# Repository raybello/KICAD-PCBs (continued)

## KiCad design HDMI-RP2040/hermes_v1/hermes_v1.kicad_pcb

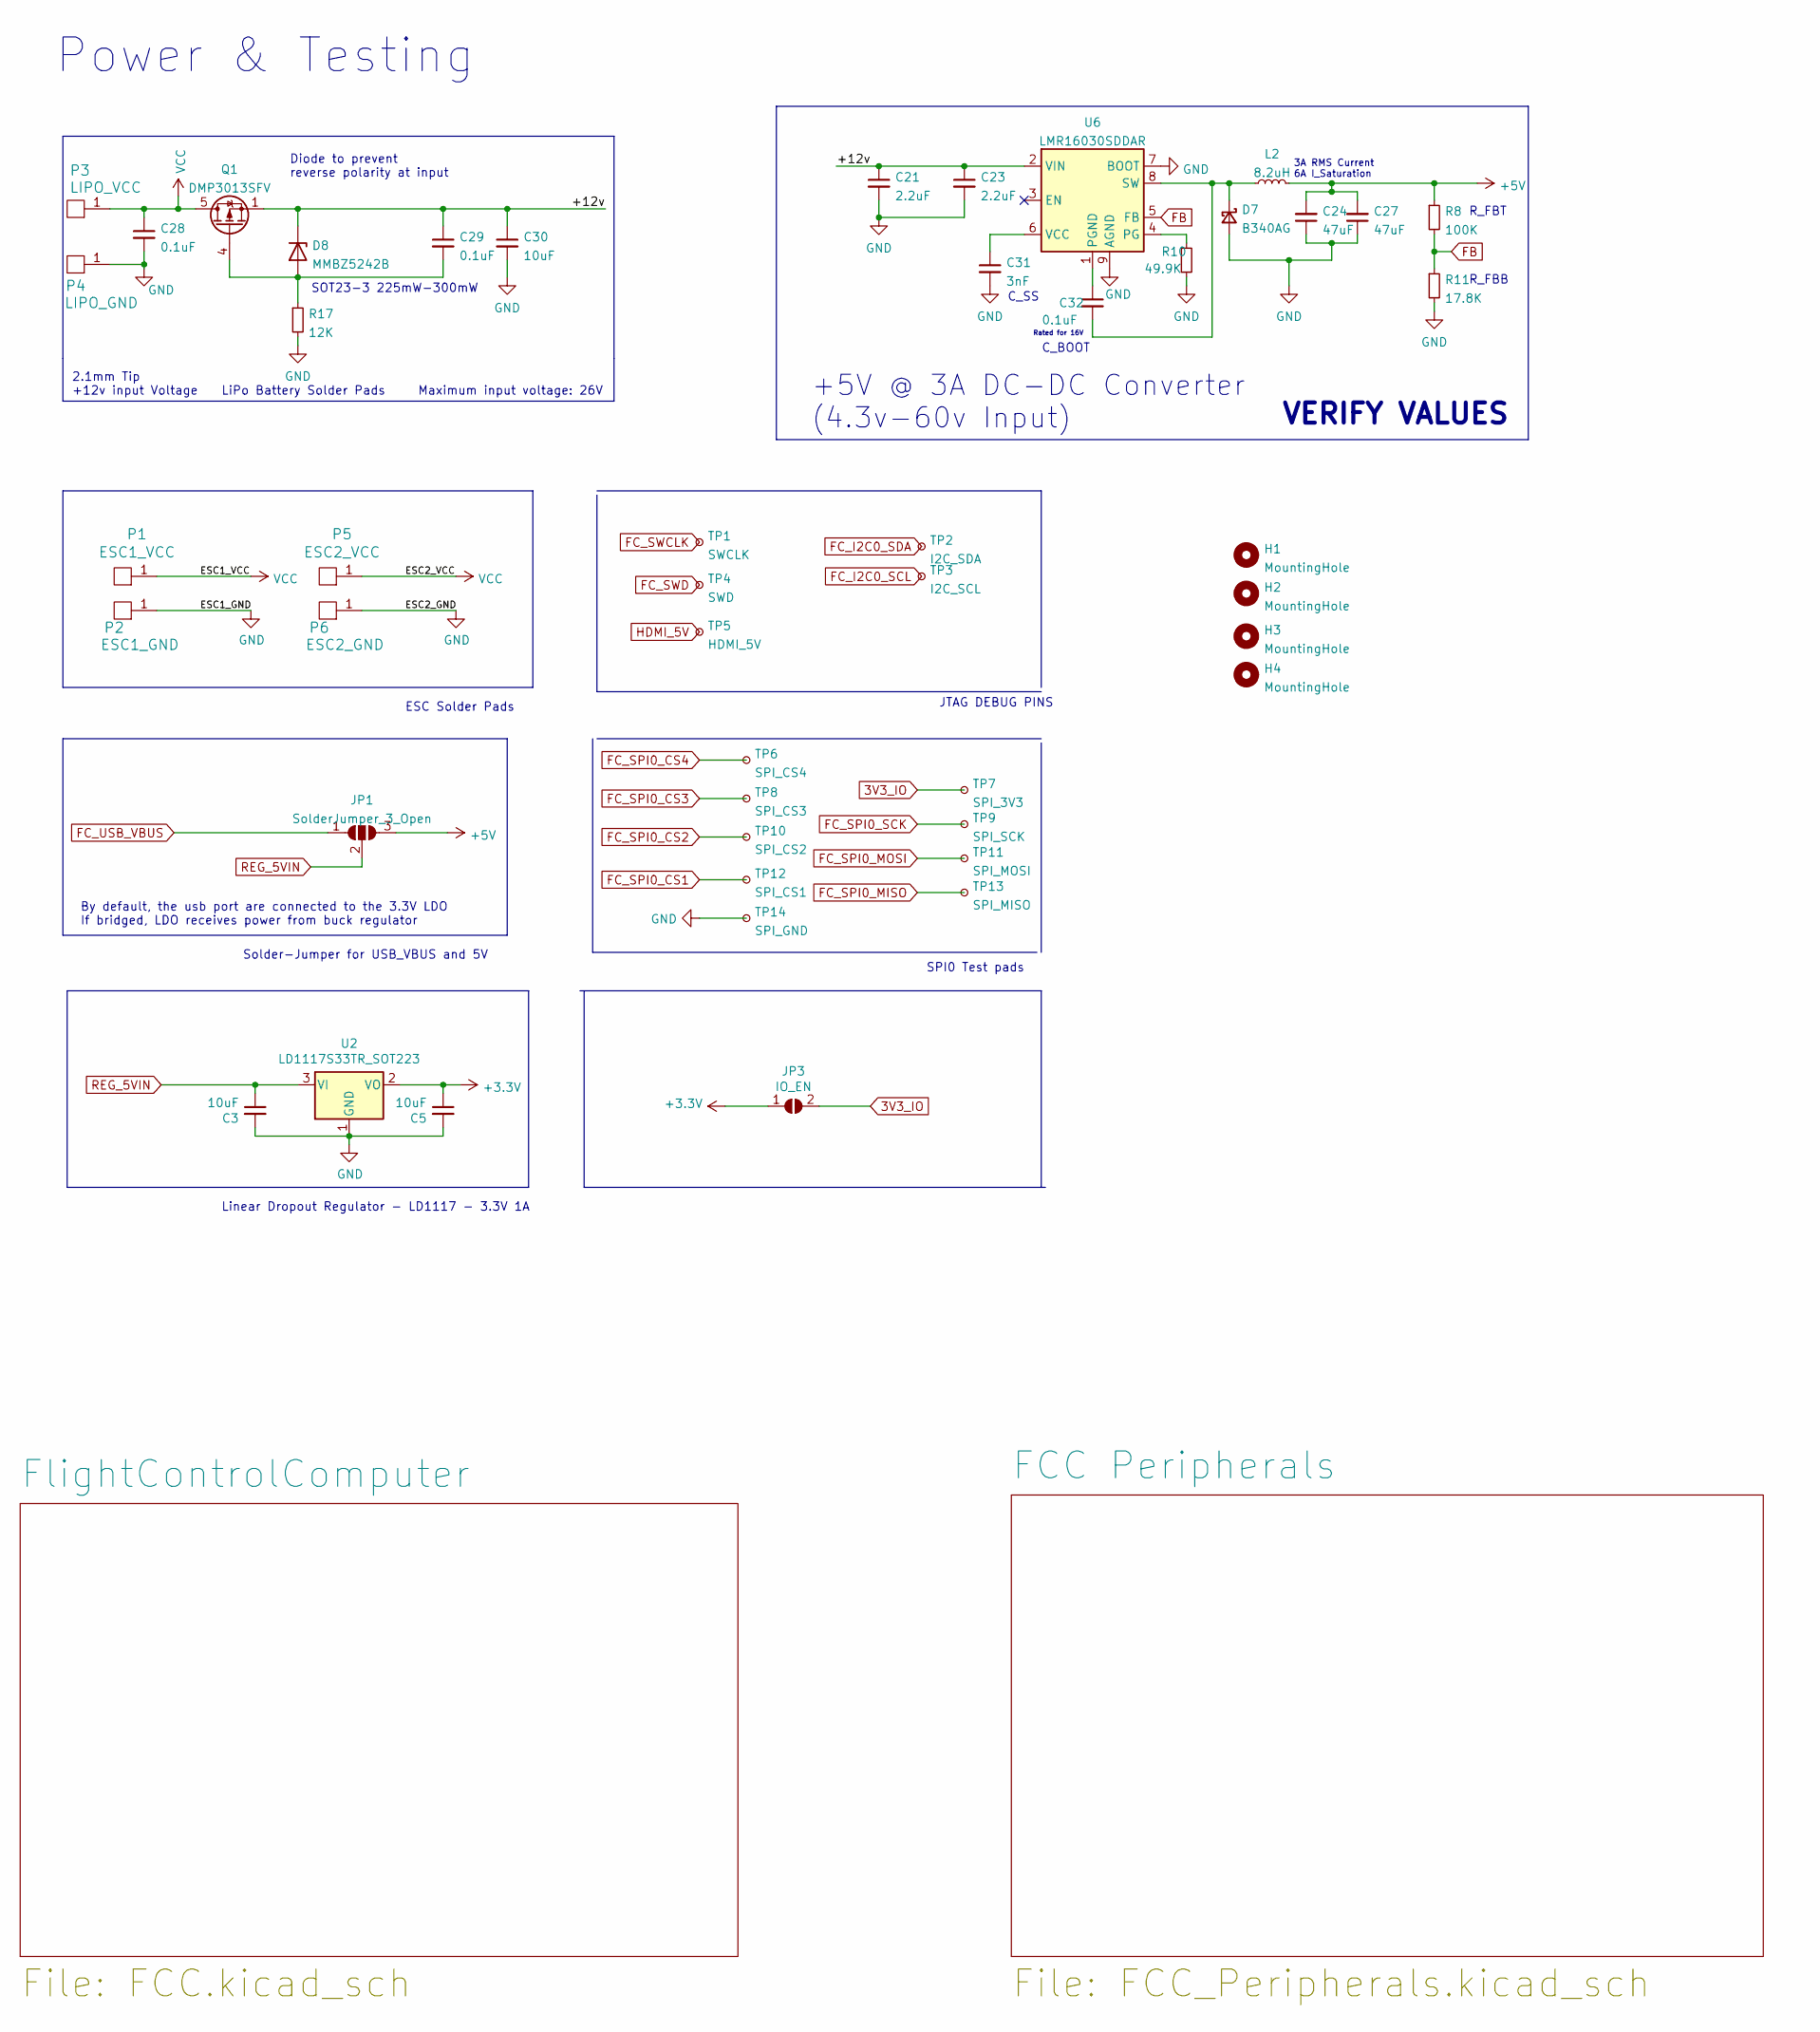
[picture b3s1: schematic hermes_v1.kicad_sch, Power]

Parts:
C3, C5: 10uF; C_0402_1005Metric_Pad0.74x0.62mm_HandSolder; LCSC C315248
C21, C23: 2.2uF; C_0402_1005Metric; LCSC C385887
C24, C27: 47uF; C_0402_1005Metric; LCSC C16780
C28, C29, C32: 0.1uF; C_0402_1005Metric; LCSC C129131
C30: 10uF; C_0402_1005Metric; LCSC C315248
C31: 3nF; C_0402_1005Metric; LCSC C2857967
D7: B340AG; D_SMB; LCSC C433997
D8: MMBZ5242B; D_SOT-23_ANK; LCSC C193729
H1, H2, H3, H4: MountingHole; MountingHole_3mm_Pad
JP1: SolderJumper_3_Open; SolderJumper-3_P1.3mm_Open_RoundedPad1.0x1.5mm_NumberLabels
JP3: IO_EN; SolderJumper-2_P1.3mm_Open_RoundedPad1.0x1.5mm
L2: 8.2uH; L_Bourns_SRP7028A_7.3x6.6mm; LCSC Mouser 652-SRP7028AA-8R2M
P1: ESC1_VCC; TestPoint_Pad_2.0x2.0mm
P2: ESC1_GND; TestPoint_Pad_D2.0mm
P3: LIPO_VCC; TestPoint_Pad_2.0x2.0mm
P4: LIPO_GND; TestPoint_Pad_D2.0mm
P5: ESC2_VCC; TestPoint_Pad_2.0x2.0mm
P6: ESC2_GND; TestPoint_Pad_D2.0mm
Q1: DMP3013SFV; Diodes_PowerDI3333-8; LCSC C461072
R8: 100K; R_0402_1005Metric; LCSC C144809
R10: 49.9K; R_0402_1005Metric; LCSC C2906873
R11: 17.8K; R_0402_1005Metric; LCSC C77605
R17: 12K; R_0402_1005Metric; LCSC C2909316
TP1: SWCLK; TestPoint_Pad_D1.0mm
TP2: I2C_SDA; TestPoint_Pad_D1.0mm
TP3: I2C_SCL; TestPoint_Pad_D1.0mm
TP4: SWD; TestPoint_Pad_D1.0mm
TP5: HDMI_5V; TestPoint_Pad_D1.0mm
TP6: SPI_CS4; TestPoint_Pad_D1.0mm
TP7: SPI_3V3; TestPoint_Pad_D1.0mm
TP8: SPI_CS3; TestPoint_Pad_D1.0mm
TP9: SPI_SCK; TestPoint_Pad_D1.0mm
TP10: SPI_CS2; TestPoint_Pad_D1.0mm
TP11: SPI_MOSI; TestPoint_Pad_D1.0mm
TP12: SPI_CS1; TestPoint_Pad_D1.0mm
TP13: SPI_MISO; TestPoint_Pad_D1.0mm
TP14: SPI_GND; TestPoint_Pad_D1.0mm
U2: LD1117S33TR_SOT223; SOT-223-3_TabPin2; LCSC C347229
U6: LMR16030SDDAR; Texas_HSOP-8-1EP_3.9x4.9mm_P1.27mm_ThermalVias; LCSC C136648

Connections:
3V3_IO: JP3.2 (B), TP7.1; also elsewhere on the board
+3V3: C5.1, JP3.1 (A), U2.2 (VO); also elsewhere on the board
+5V: C24.2, C27.2, JP1.3 (B), L2.2, R8.1; also elsewhere on the board
/+12v: C21.1, C23.1, C29.1, C30.1, D8.1 (K), Q1.1 (S), Q1.2 (S), Q1.3 (S), U6.2 (VIN)
FB: R8.2, R11.1, U6.5 (FB)
FC_I2C0_SCL: TP3.1; also elsewhere on the board
FC_I2C0_SDA: TP2.1; also elsewhere on the board
FC_SPI0_CS1: TP12.1; also elsewhere on the board
FC_SPI0_CS2: TP10.1; also elsewhere on the board
FC_SPI0_CS3: TP8.1; also elsewhere on the board
FC_SPI0_CS4: TP6.1; also elsewhere on the board
FC_SPI0_MISO: TP13.1; also elsewhere on the board
FC_SPI0_MOSI: TP11.1; also elsewhere on the board
FC_SPI0_SCK: TP9.1; also elsewhere on the board
FC_SWCLK: TP1.1; also elsewhere on the board
FC_SWD: TP4.1; also elsewhere on the board
FC_USB_VBUS: JP1.1 (A); also elsewhere on the board
GND: C3.2, C5.2, C21.2, C23.2, C24.1, C27.1, C28.2, C30.2, C31.2, D7.2 (A), P2.1 (PAD), P4.1 (PAD), P6.1 (PAD), R10.2, R11.2, R17.2, TP14.1, U2.1 (GND), U6.7 (BOOT), U6.9 (AGND); also elsewhere on the board
HDMI_5V: TP5.1; also elsewhere on the board
unnamed: C29.2, D8.2 (A), Q1.4 (G), R17.1
unnamed: C31.1, U6.6 (VCC)
unnamed: C32.1, U6.1 (PGND)
unnamed: C32.2, D7.1 (K), L2.1, U6.8 (SW)
unnamed: R10.1, U6.4 (PG)
REG_5VIN: C3.1, JP1.2 (C), U2.3 (VI)
VCC: C28.1, P1.1 (PAD), P3.1 (PAD), P5.1 (PAD), Q1.5 (D)

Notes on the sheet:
SOT23-3 225mW-300mW
R_FBB
2.1mm Tip +12v input Voltage
Maximum input voltage: 26V
SPI0 Test pads
R_FBT
Power & Testing
Rated for 16V
C_SS
+5V @ 3A DC-DC Converter (4.3v-60v Input)
C_BOOT
3A RMS Current 6A I_Saturation
LiPo Battery Solder Pads
VERIFY VALUES
Diode to prevent reverse polarity at input
Solder-Jumper for USB_VBUS and 5V
By default, the usb port are connected to the 3.3V LDO If bridged, LDO receives power from buck regulator
JTAG DEBUG PINS
ESC Solder Pads
Linear Dropout Regulator - LD1117 - 3.3V 1A

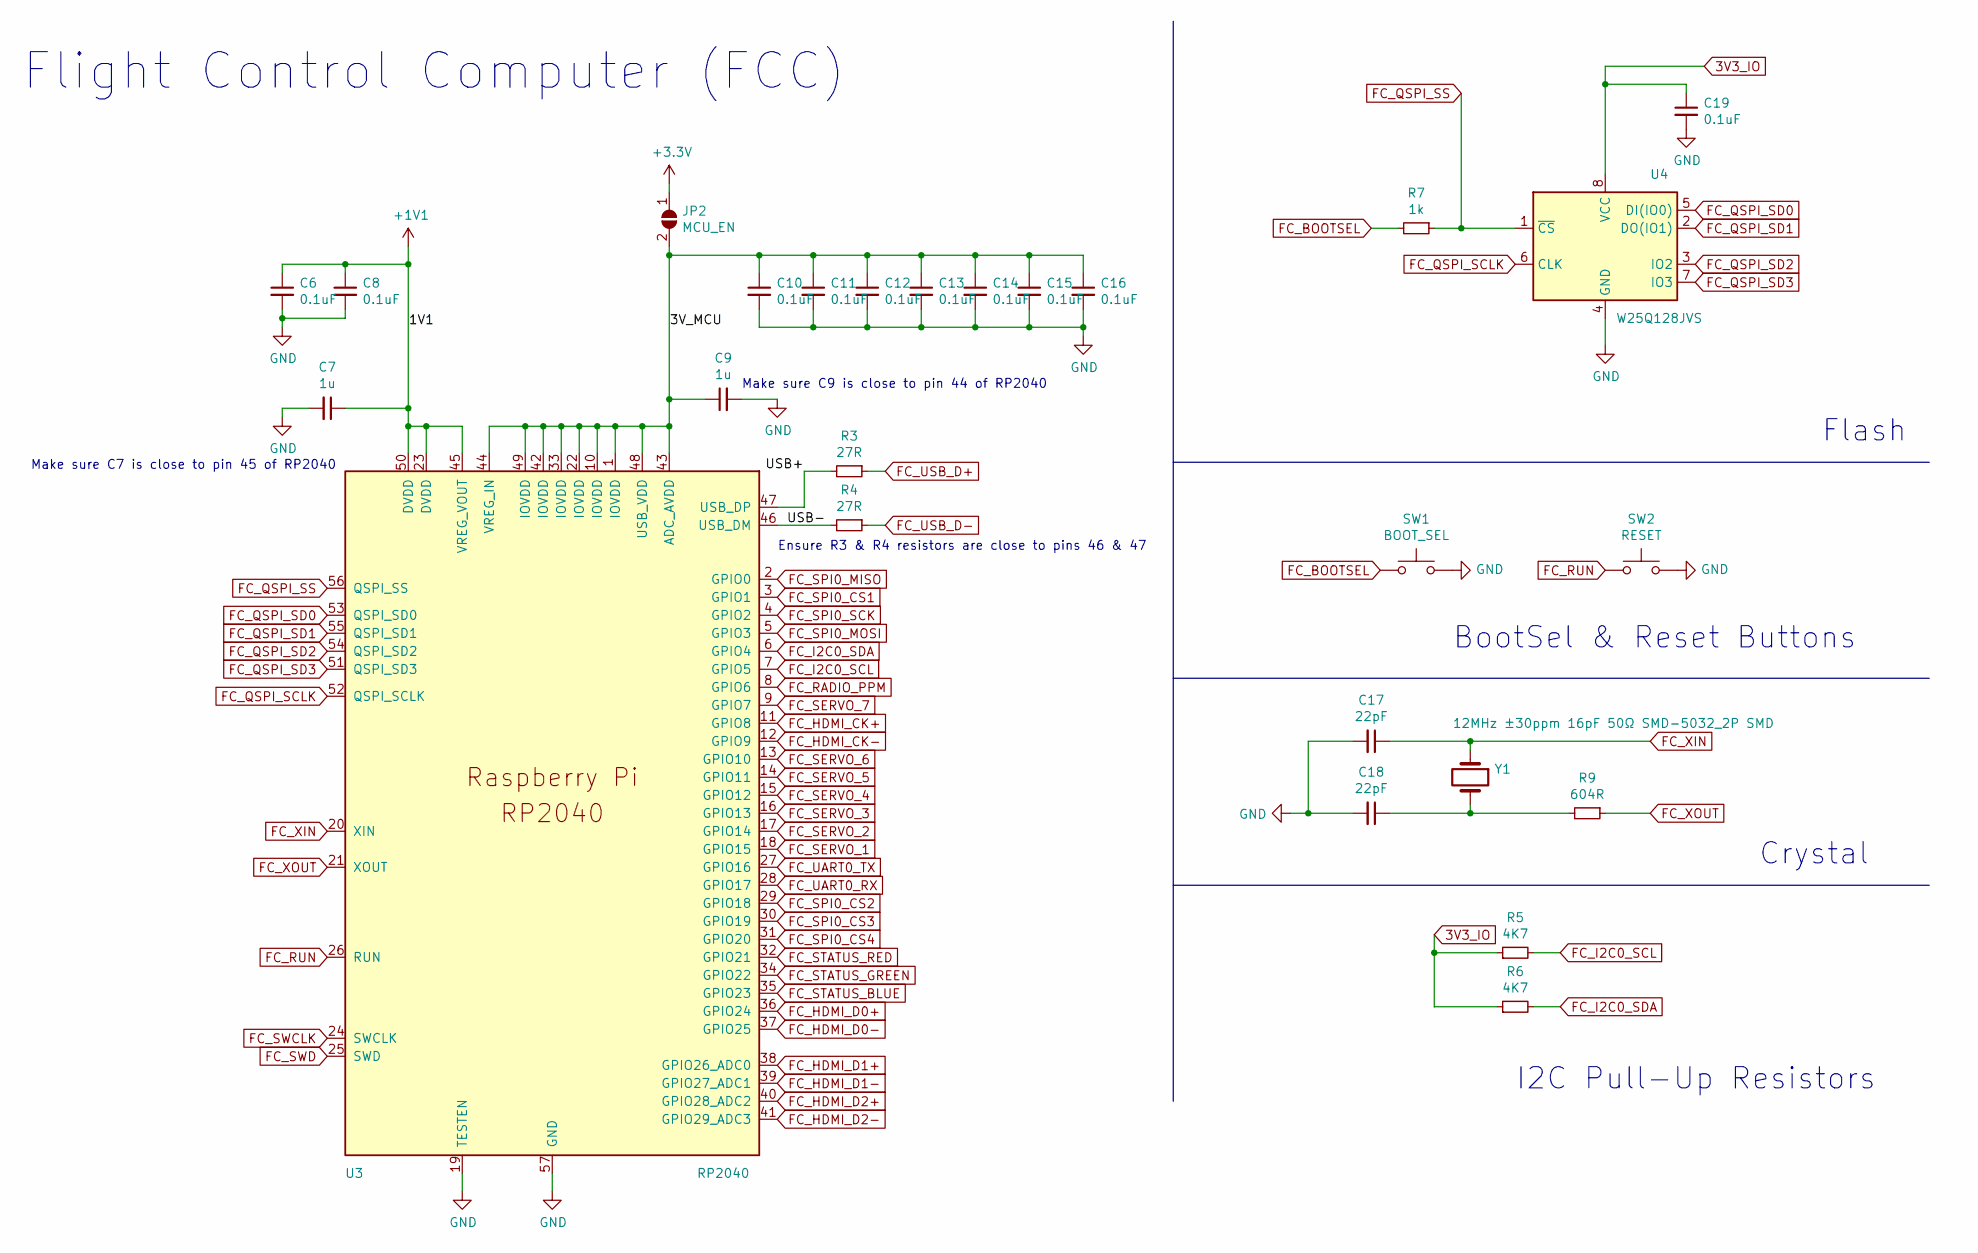
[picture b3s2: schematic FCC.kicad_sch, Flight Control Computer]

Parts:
C6, C8, C10, C11, C12, C13, C14, C15, C16, C19: 0.1uF; C_0402_1005Metric_Pad0.74x0.62mm_HandSolder; LCSC C129131
C7, C9: 1u; C_0402_1005Metric_Pad0.74x0.62mm_HandSolder; LCSC C92755
C17, C18: 22pF; C_0402_1005Metric_Pad0.74x0.62mm_HandSolder; LCSC C342943
JP2: MCU_EN; SolderJumper-2_P1.3mm_Open_RoundedPad1.0x1.5mm
R3, R4: 27R; R_0402_1005Metric_Pad0.72x0.64mm_HandSolder; LCSC C413051
R5, R6: 4K7; R_0402_1005Metric_Pad0.72x0.64mm_HandSolder; LCSC C304616
R7: 1k; R_0402_1005Metric_Pad0.72x0.64mm_HandSolder; LCSC C226166
R9: 604R; R_0402_1005Metric_Pad0.72x0.64mm_HandSolder; LCSC C273693
SW1: BOOT_SEL; SW_SPST_PTS810; LCSC C92589
SW2: RESET; SW_SPST_PTS810; LCSC C92589
U3: RP2040; RP2040-QFN-56; LCSC C2040
U4: W25Q128JVS; SOIC-8_5.23x5.23mm_P1.27mm; LCSC C97521
Y1: 12MHz ±30ppm 16pF 50Ω SMD-5032_2P SMD; Crystal_SMD_TXC_7A-2Pin_5x3.2mm; LCSC C90884

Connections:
3V3_IO: C19.1, R5.1, R6.1, U4.8 (VCC); also elsewhere on the board
+1V1: C6.1, C7.1, C8.1, U3.23 (DVDD), U3.45 (VREG_VOUT), U3.50 (DVDD)
+3V3: JP2.1 (A); also elsewhere on the board
/FlightControlComputer/3V_MCU: C9.1, C10.1, C11.1, C12.1, C13.1, C14.1, C15.1, C16.1, JP2.2 (B), U3.1 (IOVDD), U3.10 (IOVDD), U3.22 (IOVDD), U3.33 (IOVDD), U3.42 (IOVDD), U3.43 (ADC_AVDD), U3.44 (VREG_IN), U3.48 (USB_VDD), U3.49 (IOVDD)
/FlightControlComputer/USB+: R3.2, U3.47 (USB_DP)
/FlightControlComputer/USB-: R4.2, U3.46 (USB_DM)
FC_BOOTSEL: R7.2, SW1.1
FC_HDMI_CK+: U3.11 (GPIO8); also elsewhere on the board
FC_HDMI_CK-: U3.12 (GPIO9); also elsewhere on the board
FC_HDMI_D0+: U3.36 (GPIO24); also elsewhere on the board
FC_HDMI_D0-: U3.37 (GPIO25); also elsewhere on the board
FC_HDMI_D1+: U3.38 (GPIO26_ADC0); also elsewhere on the board
FC_HDMI_D1-: U3.39 (GPIO27_ADC1); also elsewhere on the board
FC_HDMI_D2+: U3.40 (GPIO28_ADC2); also elsewhere on the board
FC_HDMI_D2-: U3.41 (GPIO29_ADC3); also elsewhere on the board
FC_I2C0_SCL: R5.2, U3.7 (GPIO5); also elsewhere on the board
FC_I2C0_SDA: R6.2, U3.6 (GPIO4); also elsewhere on the board
FC_QSPI_SCLK: U3.52 (QSPI_SCLK), U4.6 (CLK)
FC_QSPI_SD0: U3.53 (QSPI_SD0), U4.5 (DI(IO0))
FC_QSPI_SD1: U3.55 (QSPI_SD1), U4.2 (DO(IO1))
FC_QSPI_SD2: U3.54 (QSPI_SD2), U4.3 (IO2)
FC_QSPI_SD3: U3.51 (QSPI_SD3), U4.7 (IO3)
FC_QSPI_SS: R7.1, U3.56 (QSPI_SS), U4.1 (~CS)
FC_RADIO_PPM: U3.8 (GPIO6); also elsewhere on the board
FC_RUN: SW2.1, U3.26 (RUN)
FC_SERVO_1: U3.18 (GPIO15); also elsewhere on the board
FC_SERVO_2: U3.17 (GPIO14); also elsewhere on the board
FC_SERVO_3: U3.16 (GPIO13); also elsewhere on the board
FC_SERVO_4: U3.15 (GPIO12); also elsewhere on the board
FC_SERVO_5: U3.14 (GPIO11); also elsewhere on the board
FC_SERVO_6: U3.13 (GPIO10); also elsewhere on the board
FC_SERVO_7: U3.9 (GPIO7); also elsewhere on the board
FC_SPI0_CS1: U3.3 (GPIO1); also elsewhere on the board
FC_SPI0_CS2: U3.29 (GPIO18); also elsewhere on the board
FC_SPI0_CS3: U3.30 (GPIO19); also elsewhere on the board
FC_SPI0_CS4: U3.31 (GPIO20); also elsewhere on the board
FC_SPI0_MISO: U3.2 (GPIO0); also elsewhere on the board
FC_SPI0_MOSI: U3.5 (GPIO3); also elsewhere on the board
FC_SPI0_SCK: U3.4 (GPIO2); also elsewhere on the board
FC_STATUS_BLUE: U3.35 (GPIO23); also elsewhere on the board
FC_STATUS_GREEN: U3.34 (GPIO22); also elsewhere on the board
FC_STATUS_RED: U3.32 (GPIO21); also elsewhere on the board
FC_SWCLK: U3.24 (SWCLK); also elsewhere on the board
FC_SWD: U3.25 (SWD); also elsewhere on the board
FC_UART0_RX: U3.28 (GPIO17); also elsewhere on the board
FC_UART0_TX: U3.27 (GPIO16); also elsewhere on the board
FC_USB_D+: R3.1; also elsewhere on the board
FC_USB_D-: R4.1; also elsewhere on the board
FC_XIN: C17.1, U3.20 (XIN), Y1.1
FC_XOUT: R9.1, U3.21 (XOUT)
GND: C6.2, C7.2, C8.2, C9.2, C10.2, C11.2, C12.2, C13.2, C14.2, C15.2, C16.2, C17.2, C18.2, C19.2, SW1.2, SW2.2, U3.19 (TESTEN), U3.57 (GND), U4.4 (GND); also elsewhere on the board
unnamed: C18.1, R9.2, Y1.2

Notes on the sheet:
Flash
Ensure R3 & R4 resistors are close to pins 46 & 47
Flight Control Computer (FCC)
BootSel & Reset Buttons
Make sure C7 is close to pin 45 of RP2040
Make sure C9 is close to pin 44 of RP2040
Crystal
I2C Pull-Up Resistors

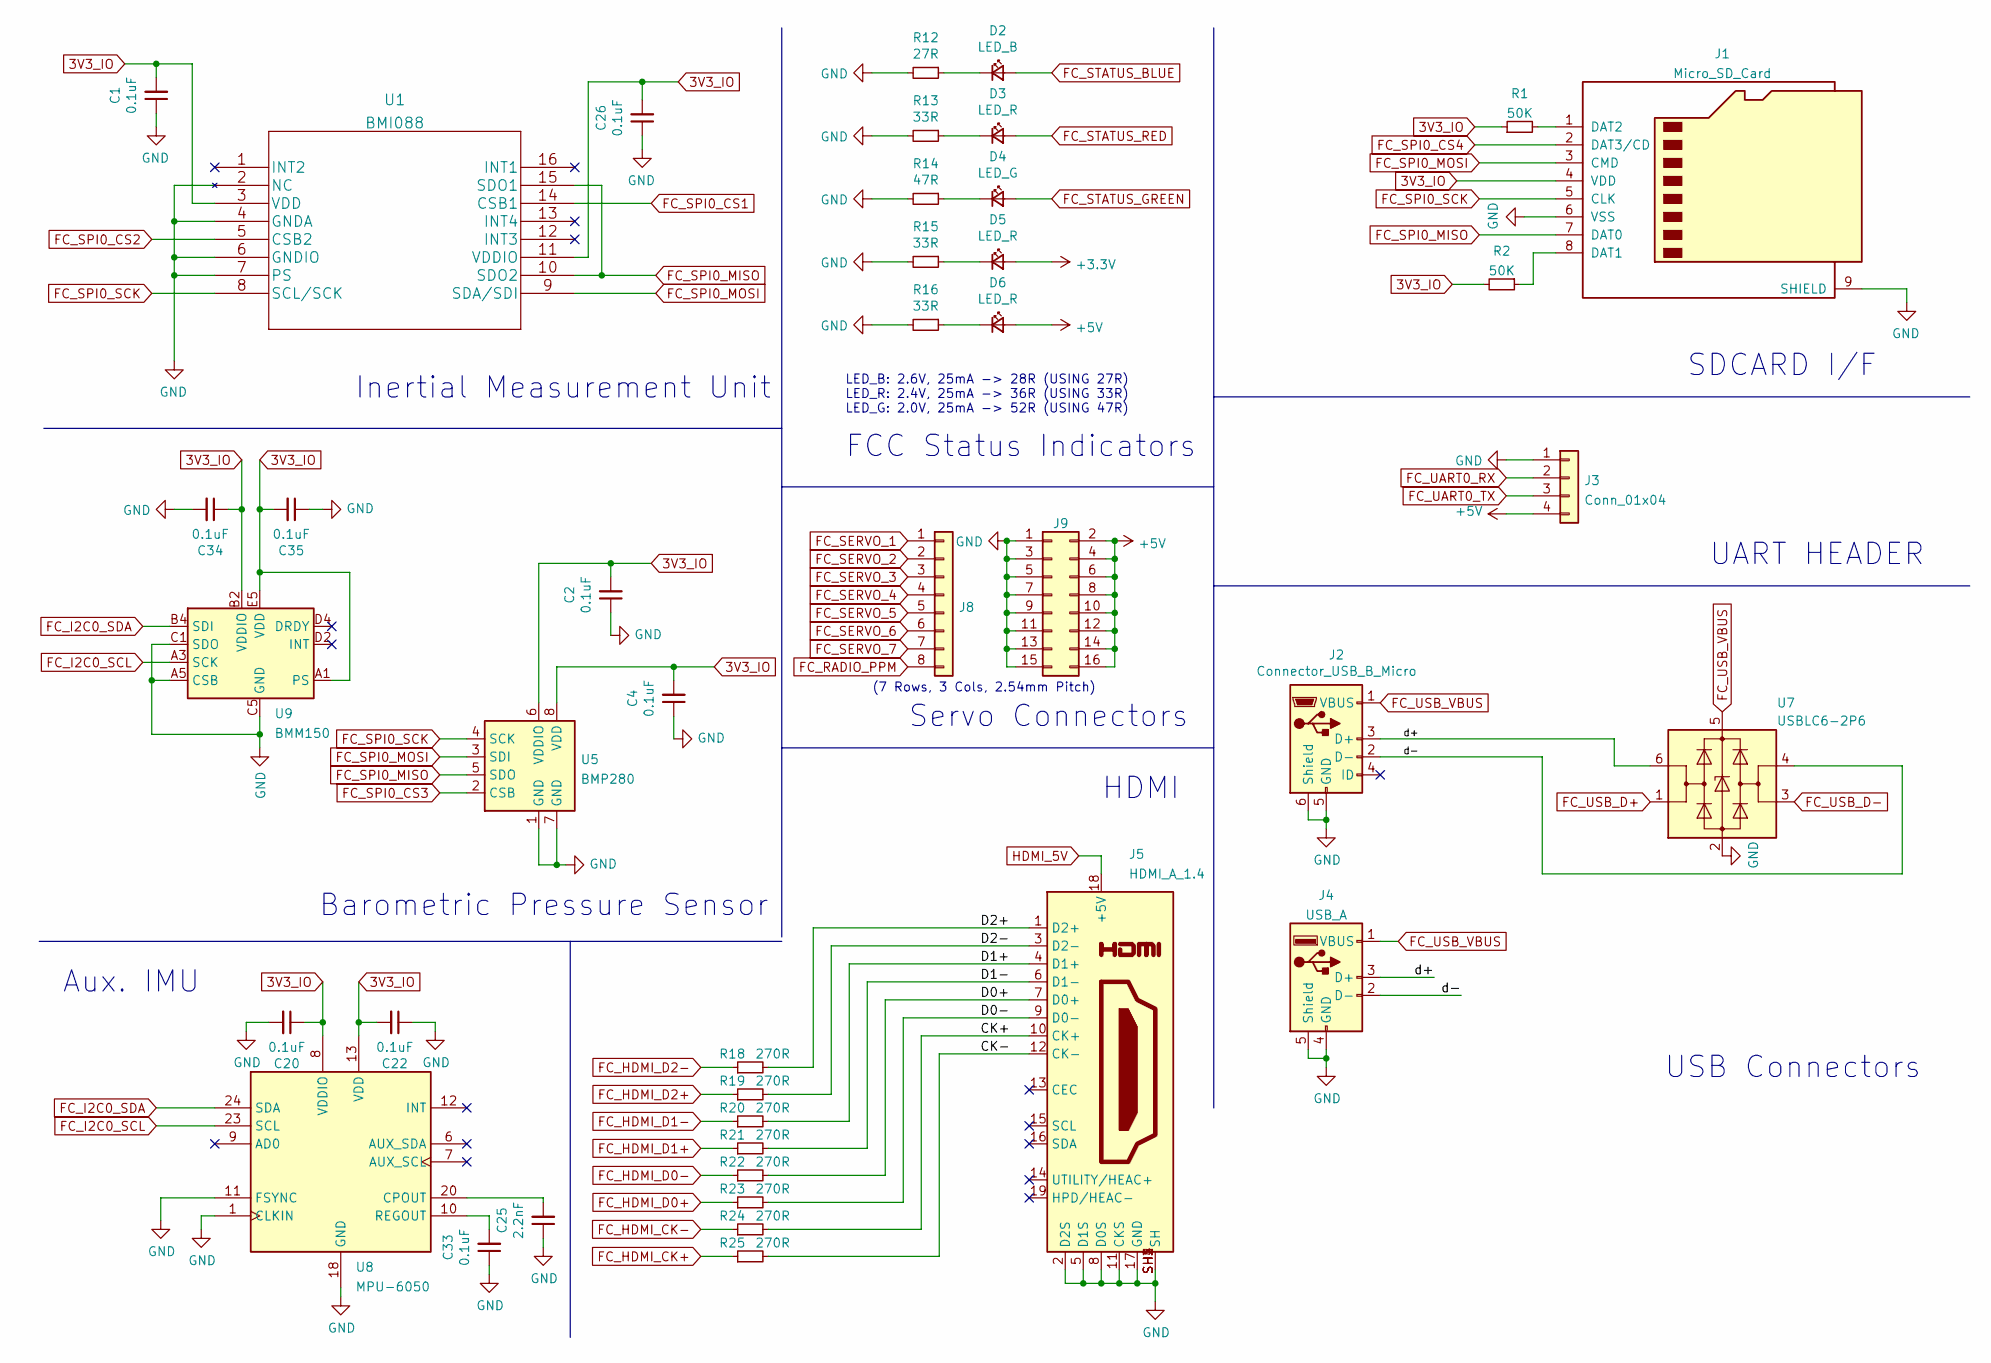
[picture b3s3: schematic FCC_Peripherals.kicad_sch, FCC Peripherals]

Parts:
C1, C2, C4, C20, C22, C26, C33, C34, C35: 0.1uF; C_0402_1005Metric_Pad0.74x0.62mm_HandSolder; LCSC C129131
C25: 2.2nF; C_0402_1005Metric_Pad0.74x0.62mm_HandSolder; LCSC C1531
D2: LED_B; LED_0402_1005Metric_Pad0.77x0.64mm_HandSolder; LCSC C434447
D3, D5, D6: LED_R; LED_0402_1005Metric_Pad0.77x0.64mm_HandSolder; LCSC C136765
D4: LED_G; LED_0402_1005Metric_Pad0.77x0.64mm_HandSolder; LCSC C434447
J1: Micro_SD_Card; microSD_HC_Wuerth_693072010801; LCSC C164170
J2: Connector_USB_B_Micro; USB_Micro-B_Amphenol_10118194_Horizontal; LCSC C132563
J3: Conn_01x04; PinHeader_1x04_P2.54mm_Vertical
J4: USB_A; USB_A_Molex_67643_Horizontal; LCSC C591765
J5: HDMI_A_1.4; EDAC 690-019-298-412; LCSC C138388
J8: Conn_01x08; PinHeader_1x08_P2.54mm_Vertical
J9: Conn_02x08_Odd_Even; PinHeader_2x08_P2.54mm_Vertical
R1, R2: 50K; R_0402_1005Metric_Pad0.72x0.64mm_HandSolder; LCSC THT PART 50K
R12: 27R; R_0402_1005Metric_Pad0.72x0.64mm_HandSolder; LCSC C413051
R13, R15, R16: 33R; R_0402_1005Metric_Pad0.72x0.64mm_HandSolder; LCSC C423285
R14: 47R; R_0402_1005Metric_Pad0.72x0.64mm_HandSolder; LCSC C25118
R18, R19, R20, R21, R22, R23, R24, R25: 270R; R_0402_1005Metric_Pad0.72x0.64mm_HandSolder; LCSC C163474 New
U1: BMI088; LCSC C194919
U5: BMP280; Bosch_LGA-8_2x2.5mm_P0.65mm_ClockwisePinNumbering; LCSC C83291
U7: USBLC6-2P6; SOT-666; LCSC C15999
U8: MPU-6050; InvenSense_QFN-24_4x4mm_P0.5mm; LCSC C50278
U9: BMM150; WLCSP-12_1.56x1.56mm_P0.4mm; LCSC C171681

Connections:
3V3_IO: C1.2, C2.2, C4.2, C20.1, C22.2, C26.2, C34.1, C35.2, J1.4 (VDD), R1.1, R2.2, U1.3 (VDD), U1.11 (VDDIO), U5.6 (VDDIO), U5.8 (VDD), U8.8 (VDDIO), U8.13 (VDD), U9.A1 (PS), U9.B2 (VDDIO), U9.E5 (VDD); also elsewhere on the board
+3V3: D5.2 (A); also elsewhere on the board
+5V: D6.2 (A), J3.4, J9.2, J9.4, J9.6, J9.8, J9.10, J9.12, J9.14, J9.16; also elsewhere on the board
/FCC Peripherals/CK+: J5.10 (CK+), R24.2
/FCC Peripherals/CK-: J5.12 (CK-), R25.2
/FCC Peripherals/D0+: J5.7 (D0+), R22.2
/FCC Peripherals/D0-: J5.9 (D0-), R23.2
/FCC Peripherals/D1+: J5.4 (D1+), R20.2
/FCC Peripherals/D1-: J5.6 (D1-), R21.2
/FCC Peripherals/D2+: J5.1 (D2+), R18.2
/FCC Peripherals/D2-: J5.3 (D2-), R19.2
/FCC Peripherals/d+: J2.3 (D+), J4.3 (D+), U7.6 (I/O1)
/FCC Peripherals/d-: J2.2 (D-), J4.2 (D-), U7.4 (I/O2)
FC_HDMI_CK+: R25.1; also elsewhere on the board
FC_HDMI_CK-: R24.1; also elsewhere on the board
FC_HDMI_D0+: R23.1; also elsewhere on the board
FC_HDMI_D0-: R22.1; also elsewhere on the board
FC_HDMI_D1+: R21.1; also elsewhere on the board
FC_HDMI_D1-: R20.1; also elsewhere on the board
FC_HDMI_D2+: R19.1; also elsewhere on the board
FC_HDMI_D2-: R18.1; also elsewhere on the board
FC_I2C0_SCL: U8.23 (SCL), U9.A3 (SCK); also elsewhere on the board
FC_I2C0_SDA: U8.24 (SDA), U9.B4 (SDI); also elsewhere on the board
FC_RADIO_PPM: J8.8; also elsewhere on the board
FC_SERVO_1: J8.1; also elsewhere on the board
FC_SERVO_2: J8.2; also elsewhere on the board
FC_SERVO_3: J8.3; also elsewhere on the board
FC_SERVO_4: J8.4; also elsewhere on the board
FC_SERVO_5: J8.5; also elsewhere on the board
FC_SERVO_6: J8.6; also elsewhere on the board
FC_SERVO_7: J8.7; also elsewhere on the board
FC_SPI0_CS1: U1.14 (CSB1); also elsewhere on the board
FC_SPI0_CS2: U1.5 (CSB2); also elsewhere on the board
FC_SPI0_CS3: U5.2 (CSB); also elsewhere on the board
FC_SPI0_CS4: J1.2 (DAT3/CD); also elsewhere on the board
FC_SPI0_MISO: J1.7 (DAT0), U1.10 (SDO2), U1.15 (SDO1), U5.5 (SDO); also elsewhere on the board
FC_SPI0_MOSI: J1.3 (CMD), U1.9 (SDA/SDI), U5.3 (SDI); also elsewhere on the board
FC_SPI0_SCK: J1.5 (CLK), U1.8 (SCL/SCK), U5.4 (SCK); also elsewhere on the board
FC_STATUS_BLUE: D2.2 (A); also elsewhere on the board
FC_STATUS_GREEN: D4.2 (A); also elsewhere on the board
FC_STATUS_RED: D3.2 (A); also elsewhere on the board
FC_UART0_RX: J3.2; also elsewhere on the board
FC_UART0_TX: J3.3; also elsewhere on the board
FC_USB_D+: U7.1 (I/O1); also elsewhere on the board
FC_USB_D-: U7.3 (I/O2); also elsewhere on the board
FC_USB_VBUS: J2.1 (VBUS), J4.1 (VBUS), U7.5 (VBUS); also elsewhere on the board
GND: C1.1, C2.1, C4.1, C20.2, C22.1, C25.1, C26.1, C33.1, C34.2, C35.1, J1.6 (VSS), J1.9 (SHIELD), J2.5 (GND), J2.6 (Shield), J3.1, J4.4 (GND), J4.5 (Shield), J5.2 (D2S), J5.5 (D1S), J5.8 (D0S), J5.11 (CKS), J5.17 (GND), J5.SH1 (SH), J5.SH2 (SH), J5.SH3 (SH), J5.SH4 (SH), J9.1, J9.3, J9.5, J9.7, J9.9, J9.11, J9.13, J9.15, R12.2, R13.2, R14.2, R15.2, R16.2, U1.2 (NC), U1.4 (GNDA), U1.6 (GNDIO), U1.7 (PS), U5.1 (GND), U5.7 (GND), U7.2 (GND), U8.1 (CLKIN), U8.11 (FSYNC), U8.18 (GND), U9.A5 (CSB), U9.C1 (SDO), U9.C5 (GND), U9.E1 (GND), U9.E3 (GND); also elsewhere on the board
HDMI_5V: J5.18 (+5V); also elsewhere on the board
unnamed: C25.2, U8.20 (CPOUT)
unnamed: C33.2, U8.10 (REGOUT)
unnamed: D2.1 (K), R12.1
unnamed: D3.1 (K), R13.1
unnamed: D4.1 (K), R14.1
unnamed: D5.1 (K), R15.1
unnamed: D6.1 (K), R16.1
unnamed: J1.1 (DAT2), R1.2
unnamed: J1.8 (DAT1), R2.1

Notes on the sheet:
HDMI
(7 Rows, 3 Cols, 2.54mm Pitch)
Barometric Pressure Sensor
Aux. IMU
Inertial Measurement Unit
FCC Status Indicators
UART HEADER
USB Connectors
SDCARD I/F
LED_B: 2.6V, 25mA -> 28R (USING 27R) LED_R: 2.4V, 25mA -> 36R (USING 33R) LED_G: 2.0V, 25mA -> 52R (USING 47R)
Servo Connectors

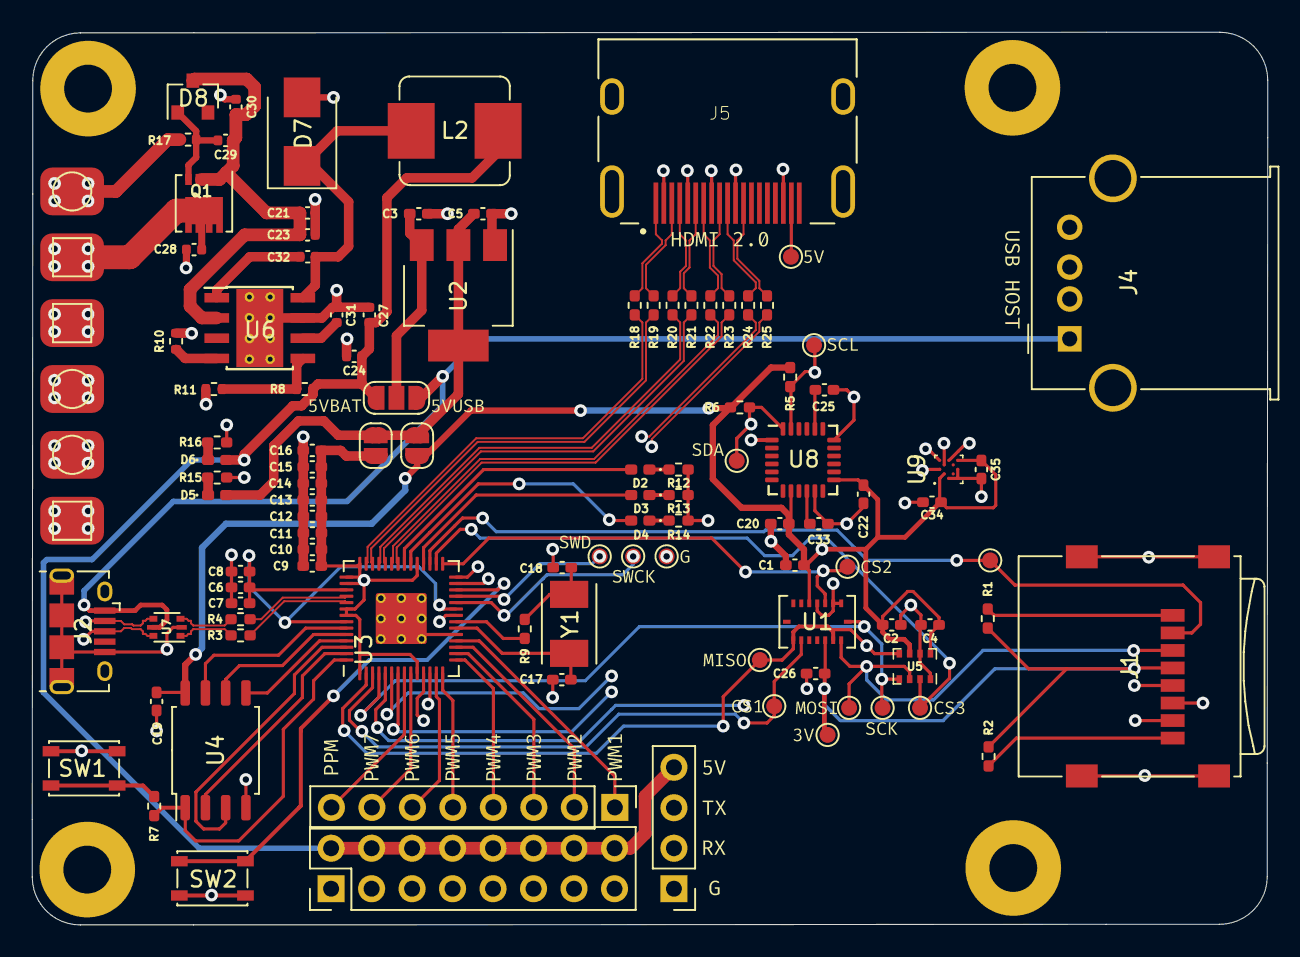
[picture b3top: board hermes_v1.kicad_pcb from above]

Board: 4 copper layers, 77.5 x 56.0 mm, 144 parts (0 on the bottom side), 83 nets.

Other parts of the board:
kibuzzard-63555CAA: G***; kibuzzard-63555CAA
kibuzzard-63555D0F: G***; kibuzzard-63555D0F
kibuzzard-635555B6: G***; kibuzzard-635555B6
kibuzzard-635555CB: G***; kibuzzard-635555CB
kibuzzard-635555EF: G***; kibuzzard-635555EF
kibuzzard-635557C8: G***; kibuzzard-635557C8
kibuzzard-635557DD: G***; kibuzzard-635557DD
kibuzzard-635558BC: G***; kibuzzard-635558BC
kibuzzard-635558D9: G***; kibuzzard-635558D9
kibuzzard-6355561B: G***; kibuzzard-6355561B
kibuzzard-6355570F: G***; kibuzzard-6355570F
kibuzzard-6355583E: G***; kibuzzard-6355583E
kibuzzard-6355586A: G***; kibuzzard-6355586A
kibuzzard-6355588E: G***; kibuzzard-6355588E
kibuzzard-6355590D: G***; kibuzzard-6355590D
kibuzzard-63555609: G***; kibuzzard-63555609
kibuzzard-63555626: G***; kibuzzard-63555626
kibuzzard-63555630: G***; kibuzzard-63555630
kibuzzard-63555640: G***; kibuzzard-63555640
kibuzzard-63555658: G***; kibuzzard-63555658
kibuzzard-63555666: G***; kibuzzard-63555666
kibuzzard-63555725: G***; kibuzzard-63555725
kibuzzard-63555742: G***; kibuzzard-63555742
kibuzzard-63555752: G***; kibuzzard-63555752
kibuzzard-63555796: G***; kibuzzard-63555796
kibuzzard-63555833: G***; kibuzzard-63555833
kibuzzard-63555878: G***; kibuzzard-63555878
kibuzzard-63555924: G***; kibuzzard-63555924
kibuzzard-63555973: G***; kibuzzard-63555973

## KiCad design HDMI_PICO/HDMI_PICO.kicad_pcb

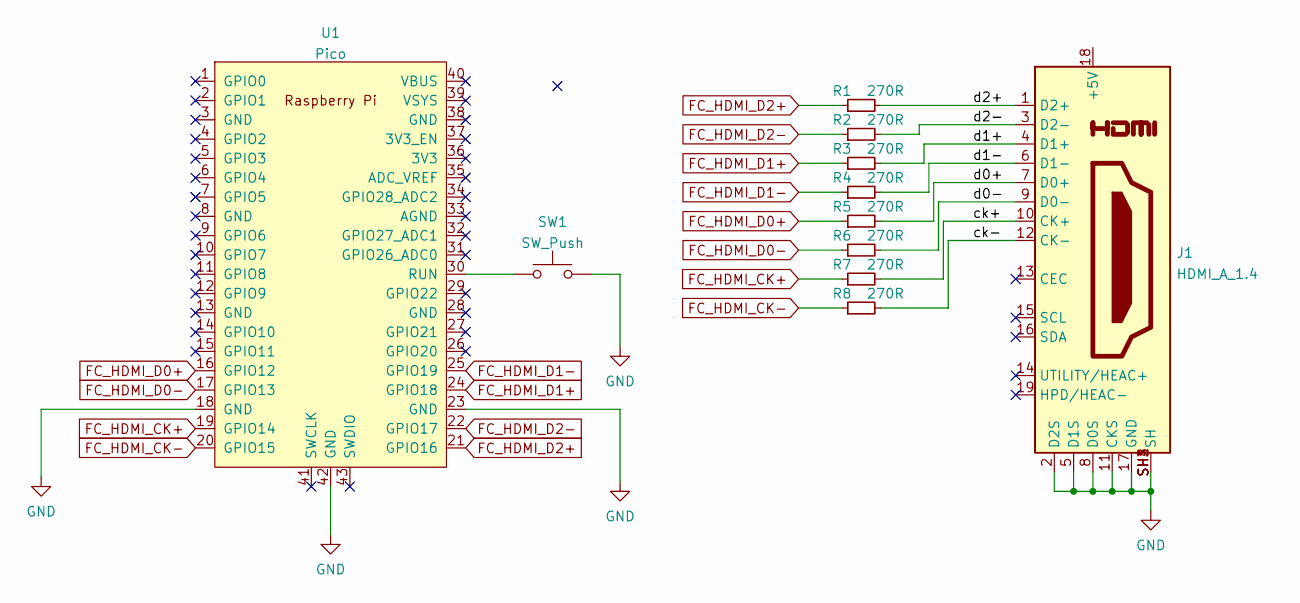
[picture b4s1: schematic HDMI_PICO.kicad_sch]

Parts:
J1: HDMI_A_1.4; EDAC 690-019-298-412
R1, R2, R3, R4, R5, R6, R7, R8: 270R; R_0402_1005Metric_Pad0.72x0.64mm_HandSolder
SW1: SW_Push; SW_SPST_PTS810
U1: Pico; RPi_Pico_SMD_TH

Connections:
/ck+: J1.10 (CK+), R7.2
/ck-: J1.12 (CK-), R8.2
/d0+: J1.7 (D0+), R5.2
/d0-: J1.9 (D0-), R6.2
/d1+: J1.4 (D1+), R3.2
/d1-: J1.6 (D1-), R4.2
/d2+: J1.1 (D2+), R1.2
/d2-: J1.3 (D2-), R2.2
FC_HDMI_CK+: R7.1, U1.19 (GPIO14)
FC_HDMI_CK-: R8.1, U1.20 (GPIO15)
FC_HDMI_D0+: R5.1, U1.16 (GPIO12)
FC_HDMI_D0-: R6.1, U1.17 (GPIO13)
FC_HDMI_D1+: R3.1, U1.24 (GPIO18)
FC_HDMI_D1-: R4.1, U1.25 (GPIO19)
FC_HDMI_D2+: R1.1, U1.21 (GPIO16)
FC_HDMI_D2-: R2.1, U1.22 (GPIO17)
GND: J1.2 (D2S), J1.5 (D1S), J1.8 (D0S), J1.11 (CKS), J1.17 (GND), J1.SH1 (SH), J1.SH2 (SH), J1.SH3 (SH), J1.SH4 (SH), SW1.2, U1.18 (GND), U1.23 (GND), U1.42 (GND)
unnamed: SW1.1, U1.30 (RUN)

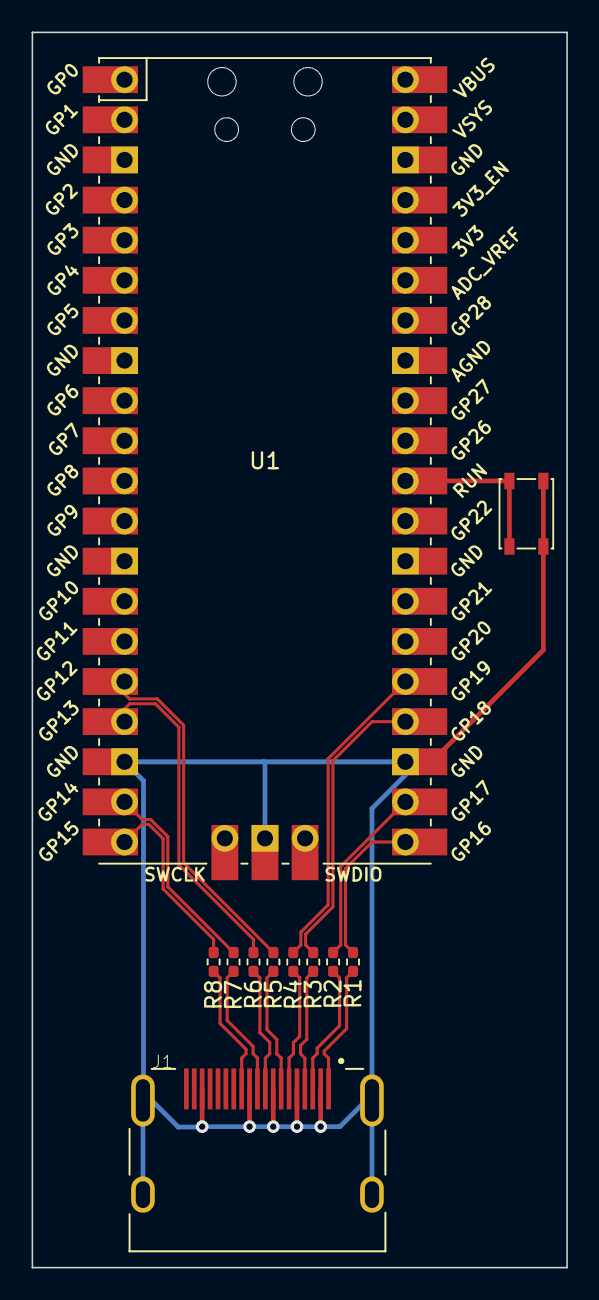
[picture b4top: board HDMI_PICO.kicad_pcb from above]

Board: 2 copper layers, 33.8 x 78.2 mm, 11 parts (0 on the bottom side), 18 nets.
